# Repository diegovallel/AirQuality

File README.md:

# AirQuality

Code of a wereable that works like a Quality Air Monitor

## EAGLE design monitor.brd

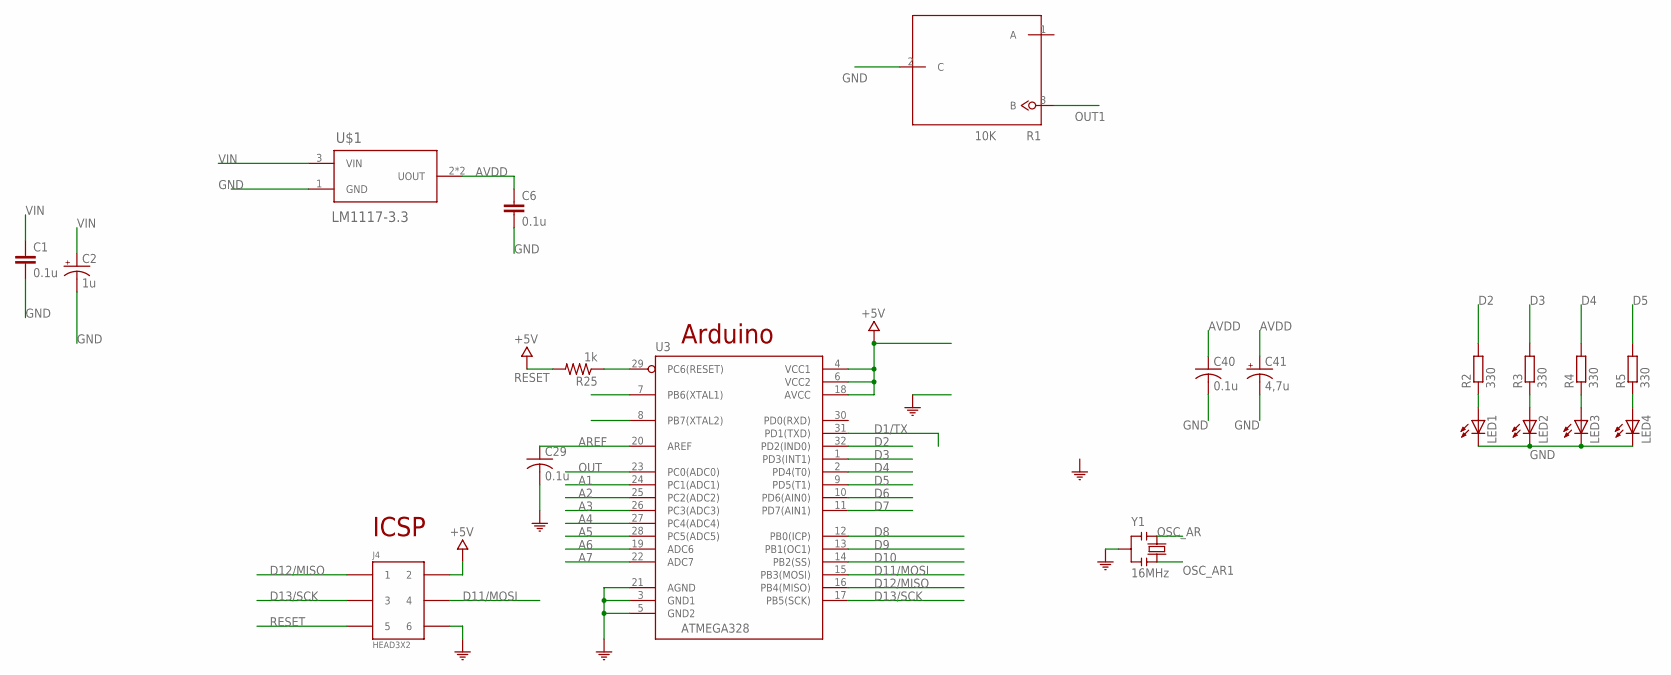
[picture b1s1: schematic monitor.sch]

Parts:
C1, C6: 0.1u; C0805
C2: 1u; B/3528-21W
C29, C40: 0.1u; C0805K
C41: 4,7u; B/3528-21W
J4: HEAD3X2
LED1, LED2, LED3, LED4: LEDCHIPLED_1206; CHIPLED_1206
R1: 10K; PACKAGE__RESISTANCE
R2, R3, R4, R5: 330; R0805
R25: 1k; M0805
U3: ATMEGA328; QFP032
U$1: LM1117-3.3; SOT-223
Y1: 16MHz; RESONATOR

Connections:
A1: U3.24 (PC1(ADC1))
A2: U3.25 (PC2(ADC2))
A3: U3.26 (PC3(ADC3))
A4: U3.27 (PC4(ADC4))
A5: U3.28 (PC5(ADC5))
A6: U3.19 (ADC6)
A7: U3.22 (ADC7)
AREF: C29.1, U3.20 (AREF)
AVDD: C6.1, C40.1, C41.+, J4.2, R25.2, U3.4 (VCC1), U3.6 (VCC2), U3.18 (AVCC), U$1.2 (UOUT), U$1.4 (UOUT)
D1/TX: U3.31 (PD1(TXD))
D2: R2.2, U3.32 (PD2(IND0))
D3: R3.2, U3.1 (PD3(INT1))
D4: R4.2, U3.2 (PD4(T0))
D5: R5.2, U3.9 (PD5(T1))
D6: U3.10 (PD6(AIN0))
D7: U3.11 (PD7(AIN1))
D8: U3.12 (PB0(ICP))
D9: U3.13 (PB1(OC1))
D10: U3.14 (PB2(SS))
D11/MOSI: J4.4, U3.15 (PB3(MOSI))
D12/MISO: J4.1, U3.16 (PB4(MISO))
D13/SCK: J4.3, U3.17 (PB5(SCK))
GND: C1.2, C2.-, C6.2, C29.2, C40.2, C41.-, J4.6, LED1.C, LED2.C, LED3.C, LED4.C, R1.2 (C), U3.3 (GND1), U3.5 (GND2), U3.21 (AGND), U$1.1 (GND), Y1.2
unnamed: LED1.A, R2.1
unnamed: LED2.A, R3.1
unnamed: LED3.A, R4.1
unnamed: LED4.A, R5.1
OSC_AR: U3.7 (PB6(XTAL1)), Y1.1
OSC_AR1: U3.8 (PB7(XTAL2)), Y1.3
OUT: U3.23 (PC0(ADC0))
OUT1: R1.3 (B)
RESET: J4.5, R25.1, U3.29 (PC6(RESET))
VIN: C1.1, C2.+, U$1.3 (VIN)

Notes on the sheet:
Arduino
ICSP

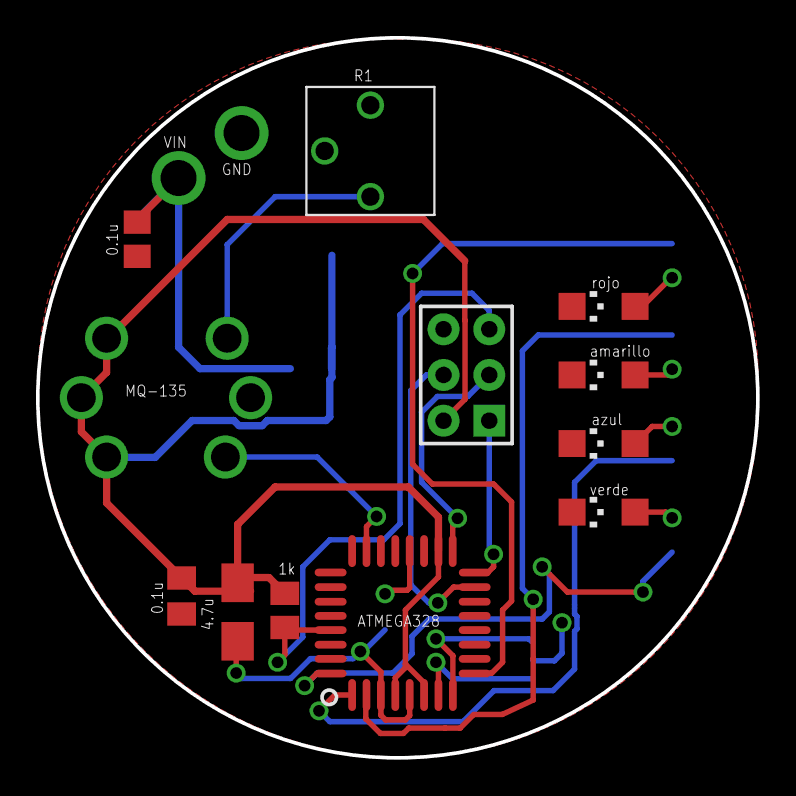
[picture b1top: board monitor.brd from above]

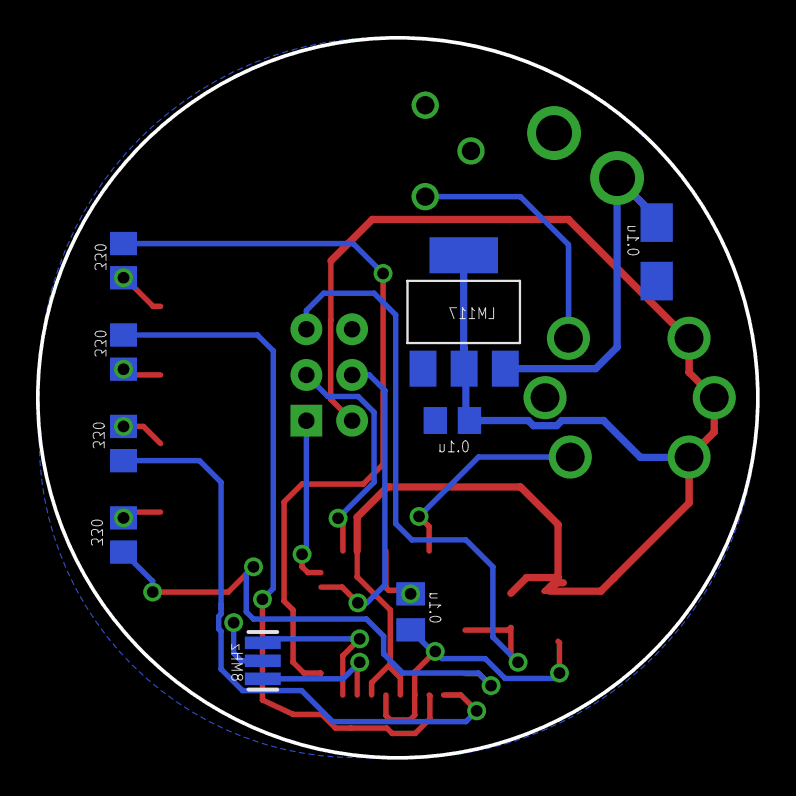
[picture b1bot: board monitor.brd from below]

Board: 2 copper layers, 40.0 x 40.0 mm, 20 parts (9 on the bottom side), 18 nets.
